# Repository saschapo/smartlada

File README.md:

# SmartLada — smart VAZ-2106 tail light

Firmware and custom hardware for a "smart" VAZ-2106 tail light: PWM dimming of the four
lamps (turn / brake / marker / reverse) with a local OLED menu, animation effects, and
**Zigbee control from a Yandex Station (Alice)**. Runs on a custom board that drops into
the light housing and is powered over **USB-C PD**.

Project page: **[smartlada.saschapo.me](https://smartlada.saschapo.me)** (source in [`site/`](site/)).

The current, primary firmware is **[`SmartLadaRevC/`](SmartLadaRevC/)** — it targets the
Rev C product board and is what the project ships. Everything else in the tree is either
the hardware design or earlier development stages (see [Lineage](#lineage)).

## Main firmware — SmartLadaRevC

ESP32-C6-WROOM-1 firmware for the Rev C board. Four PWM lamp channels (low-side MOSFET,
gamma + soft-start), an OLED menu with four buttons, pluggable effects, and a Zigbee end
device exposing five endpoints to Alice (four individual lamps + a "Fara" master/effects
device). Local control and Zigbee share one state (`config::s`, last-writer-wins).

Full details: **[`SmartLadaRevC/README.md`](SmartLadaRevC/README.md)**.

### Hardware (Rev C board)

<p align="center"><sub>Rev C, KiCad render. Top: ESP32-C6 module, buck, PD trigger, four lamp MOSFETs with
Faston outputs. Bottom: the silkscreen carries the VAZ-2106 tail-light exploded view from the parts
catalogue ("ФОНАРИ ЗАДНИЕ").</sub></p>

- **MCU:** ESP32-C6-WROOM-1-N16 (integrated on the board).
- **Power in:** USB-C PD, **12 V / 3 A trigger** (CH224K). 12 V feeds the lamps directly;
  a **TPS54202 buck** makes 3.3 V for the MCU/OLED. No 12 V → holds 5 V (logic alive, lamps dark).
  Recommended PSU: **COMMO Core** (a model with a 12 V/3 A PDO).
- **Lamp switches:** 4× AOD4184 N-MOSFET (low-side, gate active-high), outputs on **6.3 mm
  Faston tabs** with a common +12 V. Lamps: 12 V incandescent (e.g. 10+10+10+5 W).
- **UI:** SSD1315 OLED (I²C) + 4 buttons on connector J4, cabled out of the housing.
- **Diagnostics:** 6× red 0805 LEDs (4 channels + 12 V + 3.3 V); PG (power-good) → GPIO.

Board design (KiCad, BOM, fabrication): **[`custom_pcb/smartlada_revC/`](custom_pcb/smartlada_revC/)**.

### Build & flash

Zigbee end-device build, Serial over native USB:

```sh
FQBN="esp32:esp32:esp32c6:ZigbeeMode=ed,PartitionScheme=zigbee_8MB,CDCOnBoot=cdc,FlashSize=16M"
arduino-cli compile -b "$FQBN" SmartLadaRevC
arduino-cli upload  -b "$FQBN" -p /dev/cu.usbmodemXXXX SmartLadaRevC
```

Bench variant with the 2.4" TFT + encoder module in place of the OLED + keys: build flag
`UI_TFT`, see [`SmartLadaRevC/README.md`](SmartLadaRevC/README.md#bench-variant-24-tft--encoder-ui_tft).

Plan and resume notes: [`SmartLadaRevC/DEV_PLAN.md`](SmartLadaRevC/DEV_PLAN.md),
[`SmartLadaRevC/SESSION_HANDOFF.md`](SmartLadaRevC/SESSION_HANDOFF.md).

## Lineage

The firmware grew through several stages; the earlier ones are kept for reference:

- [`sketches/SmartLada/`](sketches/SmartLada/) — first bring-up bench on an **ESP8266**
  (calibration, OLED). Its `channels/` and `config/` layers seeded the ESP32 port.
- [`SmartLadaC6/`](SmartLadaC6/) — **ESP32-C6 on a MuseLab nanoESP32-C6** dev board:
  LEDC PWM, Wi-Fi AP + web UI, test modes. First C6 firmware.
- [`SmartLadaRevB/`](SmartLadaRevB/) — display-based firmware (OLED menu + effects) on the
  Rev B board; direct **predecessor to Rev C** (Rev C forks its `src/` layers).
- **[`SmartLadaRevC/`](SmartLadaRevC/)** — current product firmware (this board + Zigbee).

Hardware history lives under [`custom_pcb/`](custom_pcb/) (Rev A → Rev B → Rev C);
research and architecture notes under [`research/`](research/); experimental sketches
under [`sketches/`](sketches/).

## Project context (Russian)

Historical planning/context documents, kept in Russian on purpose:

- [`PROJECT_2106_SMART_LIGHT.md`](PROJECT_2106_SMART_LIGHT.md) — decisions, hardware, architecture, plan.
- [`VAZ2106_Smart_Lamp_Context.md`](VAZ2106_Smart_Lamp_Context.md) — earlier context document.
- [`TASK_smartlada_bench_esp8266.md`](TASK_smartlada_bench_esp8266.md) — ESP8266 bench spec (done).
- [`schematic_2106_ESP32.md`](schematic_2106_ESP32.md) — early wiring schematic.

> Chat and `.md` documentation are in Russian; firmware code, comments, and identifiers are in English.

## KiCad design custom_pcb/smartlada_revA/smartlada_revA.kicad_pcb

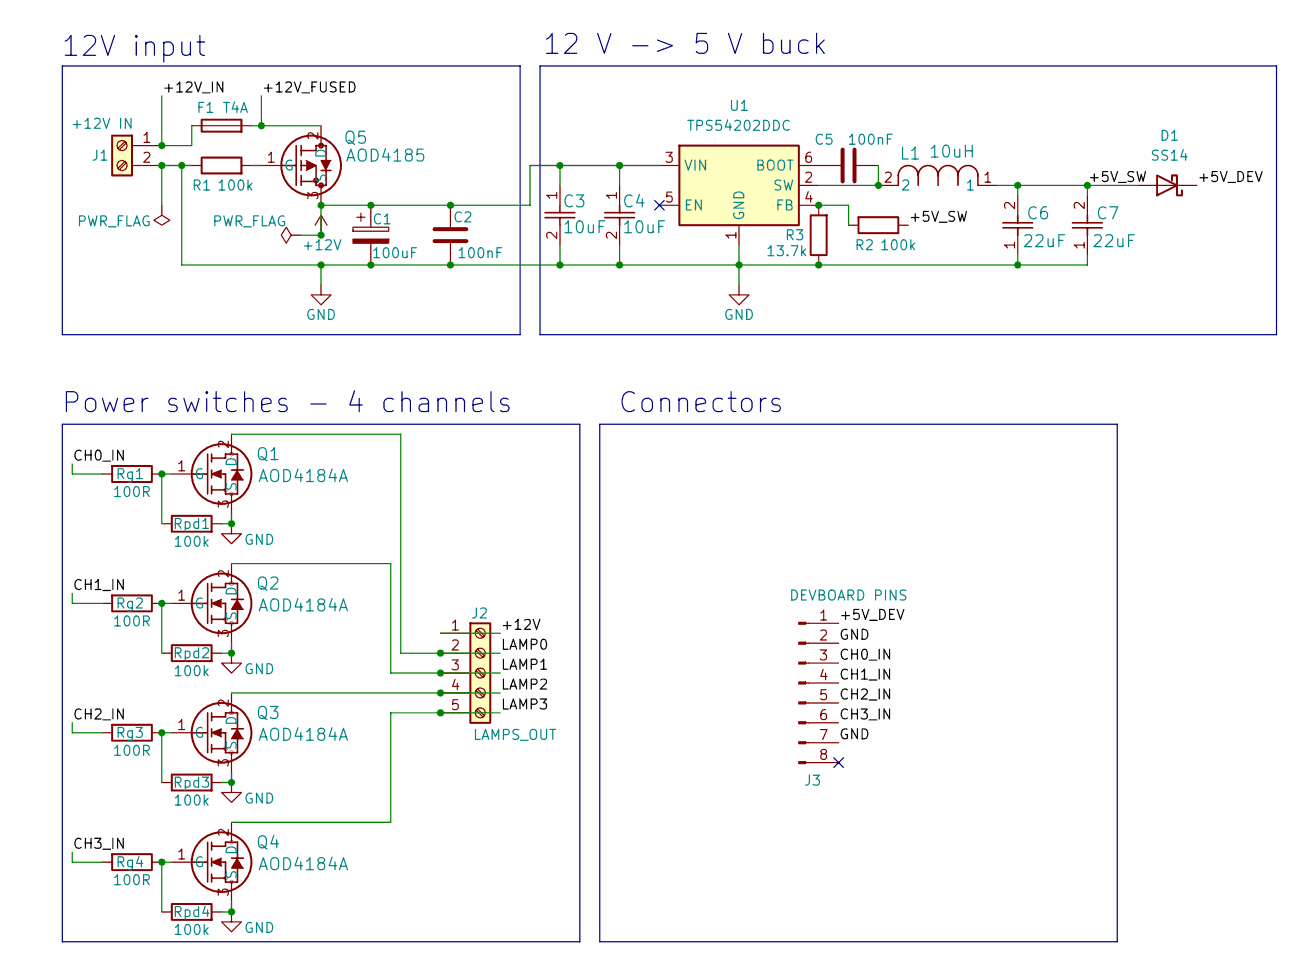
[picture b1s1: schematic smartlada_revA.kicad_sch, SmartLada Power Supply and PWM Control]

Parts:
C1: 100uF; CP_Radial_D6.3mm_P2.50mm; MPN EEUFR1E101
C2: 100nF; C_0805_2012Metric_Pad1.18x1.45mm_HandSolder; MPN GRM21BR71E104KA01L
C3, C4: 10uF; CAP_UMK325BJ106KM-P_TAY; MPN HLC1210X7R106K500N
C5: 100nF; C_0603_1608Metric_Pad1.08x0.95mm_HandSolder; MPN GRM188R72A104KA35D
C6, C7: 22uF; CAP_2012_TDK; MPN GRT21BR61E226ME13L
D1: SS14; D_SMA; MPN SS14-E3/61T
F1: T4A; Fuseholder_Cylinder-5x20mm_Schurter_0031_8201_Horizontal_Op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; MPN S1052-1
J1: +12V IN; TerminalBlock_MaiXu_MX126-5.0-02P_1x02_P5.00mm; MPN DG127-5.0-02P-14-00Z(H)
J2: LAMPS_OUT; TerminalBlock_Phoenix_MPT-0,5-5-2.54_1x05_P2.54mm_Horizontal; MPN DG308-2.54-05P-14-00ZH
J3: DEVBOARD PINS; PinHeader_1x08_P2.54mm_Vertical; MPN PLS-40 (alt L-KLS1-207-1-40-S)
L1: 10uH; IND_CDRH6D28NP-100NC_SUM; MPN CDRH6D28NP-100NC
Q1, Q2, Q3, Q4: AOD4184A; TO252_AOS; MPN AOD4184A
Q5: AOD4185; TO252_AOS; MPN AOD4185
R1, R2: 100k; R_0805_2012Metric_Pad1.20x1.40mm_HandSolder; MPN ERJP06F1003V
R3: 13.7k; R_0805_2012Metric_Pad1.20x1.40mm_HandSolder; MPN RC0805FR-0713K7L
Rg1, Rg2, Rg3, Rg4: 100R; R_0805_2012Metric_Pad1.20x1.40mm_HandSolder; MPN RT0805BRD07100RL
Rpd1, Rpd2, Rpd3, Rpd4: 100k; R_0805_2012Metric_Pad1.20x1.40mm_HandSolder; MPN ERJP06F1003V
U1: TPS54202DDC; SOT-23-6; MPN TPS54202DDCR

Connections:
+12V: C1.1, C2.1, C3.1, C4.1, J2.1, Q5.3 (S), U1.3 (VIN)
/+5V_DEV: D1.1 (K), J3.1
/+5V_SW: C6.2, C7.2, D1.2 (A), L1.1, R2.1
/+12V_FUSED: F1.2, Q5.2 (D)
/+12V_IN: F1.1, J1.1
/CH0_IN: J3.3, Rg1.2
/CH1_IN: J3.4, Rg2.2
/CH2_IN: J3.5, Rg3.2
/CH3_IN: J3.6, Rg4.2
/LAMP0: J2.2, Q1.2 (D)
/LAMP1: J2.3, Q2.2 (D)
/LAMP2: J2.4, Q3.2 (D)
/LAMP3: J2.5, Q4.2 (D)
GND: C1.2, C2.2, C3.2, C4.2, C6.1, C7.1, J1.2, J3.2, J3.7, Q1.3 (S), Q2.3 (S), Q3.3 (S), Q4.3 (S), R1.1, R3.1, Rpd1.2, Rpd2.2, Rpd3.2, Rpd4.2, U1.1 (GND)
unnamed: Q1.1 (G), Rg1.1, Rpd1.1
unnamed: Q2.1 (G), Rg2.1, Rpd2.1
unnamed: Q3.1 (G), Rg3.1, Rpd3.1
unnamed: Q4.1 (G), Rg4.1, Rpd4.1
unnamed: Q5.1 (G), R1.2
unnamed: C5.1, U1.6 (BOOT)
unnamed: R2.2, R3.2, U1.4 (FB)
unnamed: C5.2, L1.2, U1.2 (SW)

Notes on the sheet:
12V input
12 V -> 5 V buck
Connectors
Power switches - 4 channels

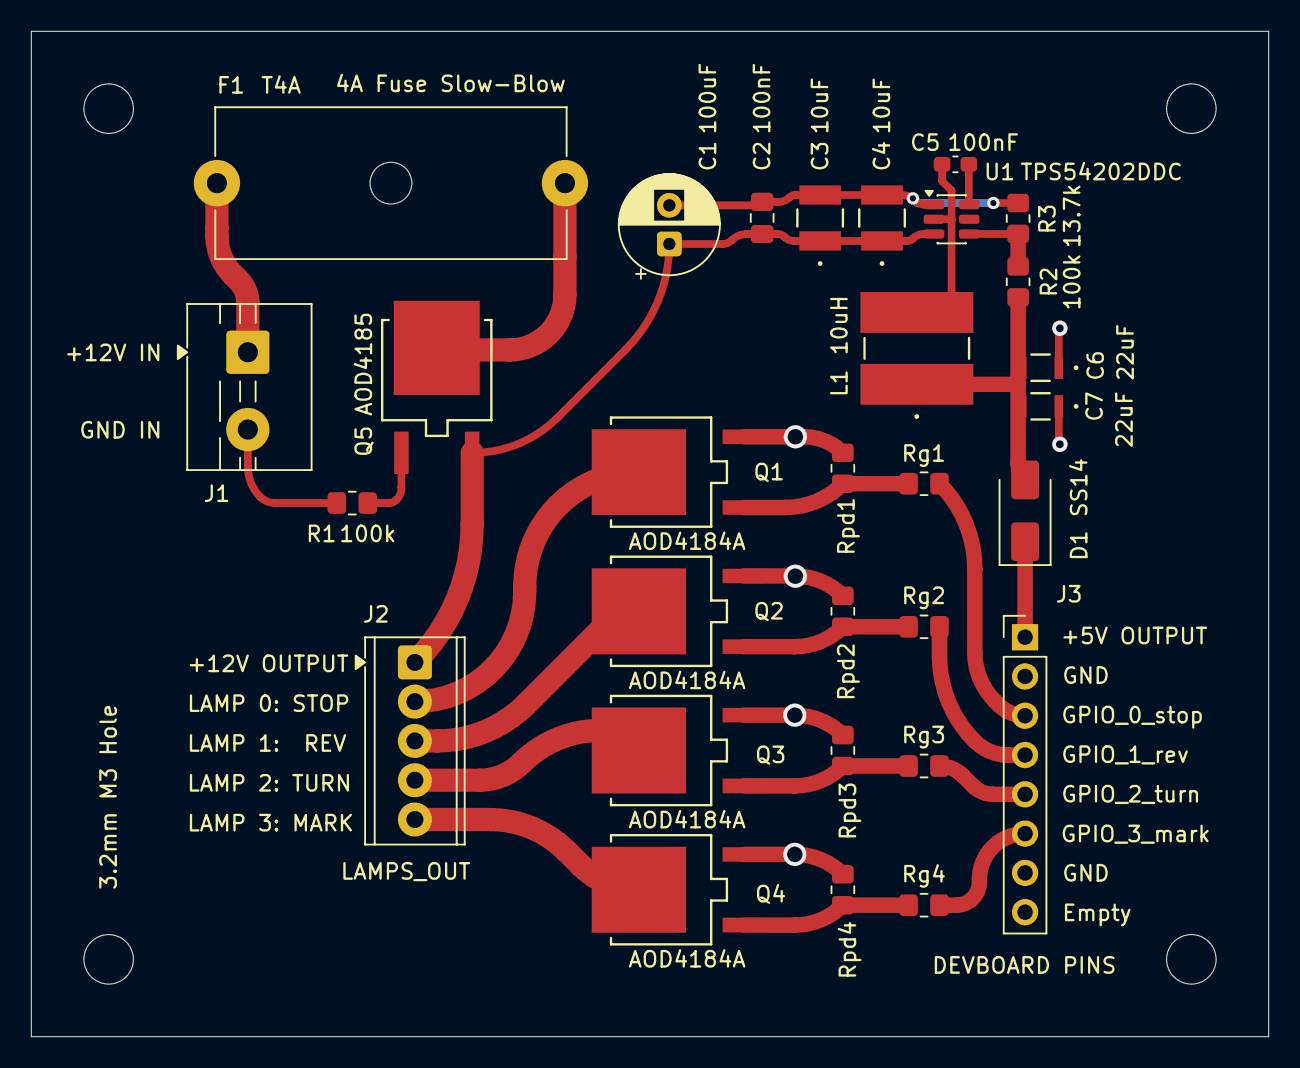
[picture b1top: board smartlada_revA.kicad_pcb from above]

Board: 2 copper layers, 80.0 x 65.0 mm, 34 parts (0 on the bottom side), 22 nets.

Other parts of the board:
H1, H2, H3: 3.2mm_M3; MountingHole_3.2mm_M3
H4: 3.2mm M3 Hole; MountingHole_3.2mm_M3

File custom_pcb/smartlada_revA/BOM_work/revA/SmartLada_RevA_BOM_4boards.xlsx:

SmartLada Rev A — комплектация на 4 платы
Источник: схема smartlada_revA (30 символов) x 4 платы. 'Нужно на 4' = формула 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
Ref | Описание / номинал | MPN | Производитель | Корпус | Кол-во/плата | Нужно на 4 | Заказать | Примечание
Q1-Q4 | MOSFET N-канал 40V (ключи ламп) | AOD4184A | Alpha & Omega | TO-252 | 4 | 16 | 20
Q5 | MOSFET P-канал (защита от переполюсовки) | AOD4185 | Alpha & Omega | TO-252 | 1 | 4 | 6 | докупить: в корзине 3
U1 | Buck 12->5V, 2A ADJ | TPS54202DDCR | Texas Instruments | SOT-23-6 | 1 | 4 | 6 | докупить: в корзине 3
L1 | Дроссель 10 uH экранир. | CDRH6D28NP-100NC | Sumida | 6x6 mm | 1 | 4 | 5 | докупить: в корзине 3
D1 | Диод Шоттки 1A 40V | SS14-E3/61T | Vishay | SMA | 1 | 4 | 8 | в корзине 20 — хватает
F1 (держатель) | Держатель предохр. 5x20 4A | S1052-1 | RUICHI | THT | 1 | 4 | 6 | OK: комплект (пластик. корпус + 2 контакта) = 1 держатель на плату
F1 (вставка) | Предохранитель T4A 5x20 медленный | FS-52GT-4.0/250 | GSL | 5x20 mm | 1 | 4 | 8 | расходник (сгорает на bring-up); докупить: в корзине 3
C1 | Электролит 100 uF 25V | EEUFR1E101 | Panasonic | D6.3 P2.5 | 1 | 4 | 6
C2 | Керам. 100 nF 25V | TCC0603X7R104K250CT | TCC | 0603 на 0805 | 1 | 4 | (в C5) | тот же TCC0603, что C5; 0603-корпус на площадке 0805 (осознанно); в общем заказе
C3,C4 | Керам. 10 uF 50V | HLC1210X7R106K500N | Walsin | 1210 | 2 | 8 | 12
C5 | Керам. 100 nF 25V (in-stock замена) | TCC0603X7R104K250CT | TCC | 0603 | 1 | 4 | 20 | C5+C2 = один TCC0603; заказ 20 на обе позиции; в наличии, от 1 шт
C6,C7 | Керам. 22 uF 25V | GRT21BR61E226ME13L | Murata | 0805 | 2 | 8 | 12
R1,R2,Rpd1-4 | Резистор 100k 1% | ERJP06F1003V | Panasonic | 0805 | 6 | 24 | 30 | докупить: в корзине 20 (нужно 24)
R3 | Резистор 13.7k 1% (делитель FB) | RC0805FR-0713K7L | Yageo | 0805 | 1 | 4 | 10
Rg1-4 | Резистор 100R (затвор) | RT0805BRD07100RL | Yageo | 0805 | 4 | 16 | 20
J1 | Клеммник 2 конт. 5.0 mm | DG127-5.0-02P-14-00Z(H) | Degson | THT | 1 | 4 | 6 | склад Platan 3 шт (нужно 4): взять 3 сейчас, +3 ДОЗАКАЗАТЬ позже
J2 | Клеммник 5 конт. 2.54 mm | DG308-2.54-05P-14-00ZH | Degson | THT | 1 | 4 | 6 | докупить: в корзине 3
J3 | Штырёк 1x40 2.54 mm (нужно 8 конт/плата) | PLS-40 (L-KLS1-207-1-40-S) | KLS | THT | 8 | 32 | 2 | единицы = контакты; заказать 2 линейки 1x40 (1 хватает на 32 конт)
Позиции AOD4184A (16), C6/C7 (8), Rg (16) в текущей корзине стоят ровно под нуж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
S1052-1: проверить, что 1 шт = комплект держателя (2 клипсы). Если продаётся по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
J3: PLS-40 считается линейками 1x40; на плату 8 контактов, на 4 платы = 32 из 4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
Заявка на изготовление плат — см. electroconnect_order_260721.md. Плат заказано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

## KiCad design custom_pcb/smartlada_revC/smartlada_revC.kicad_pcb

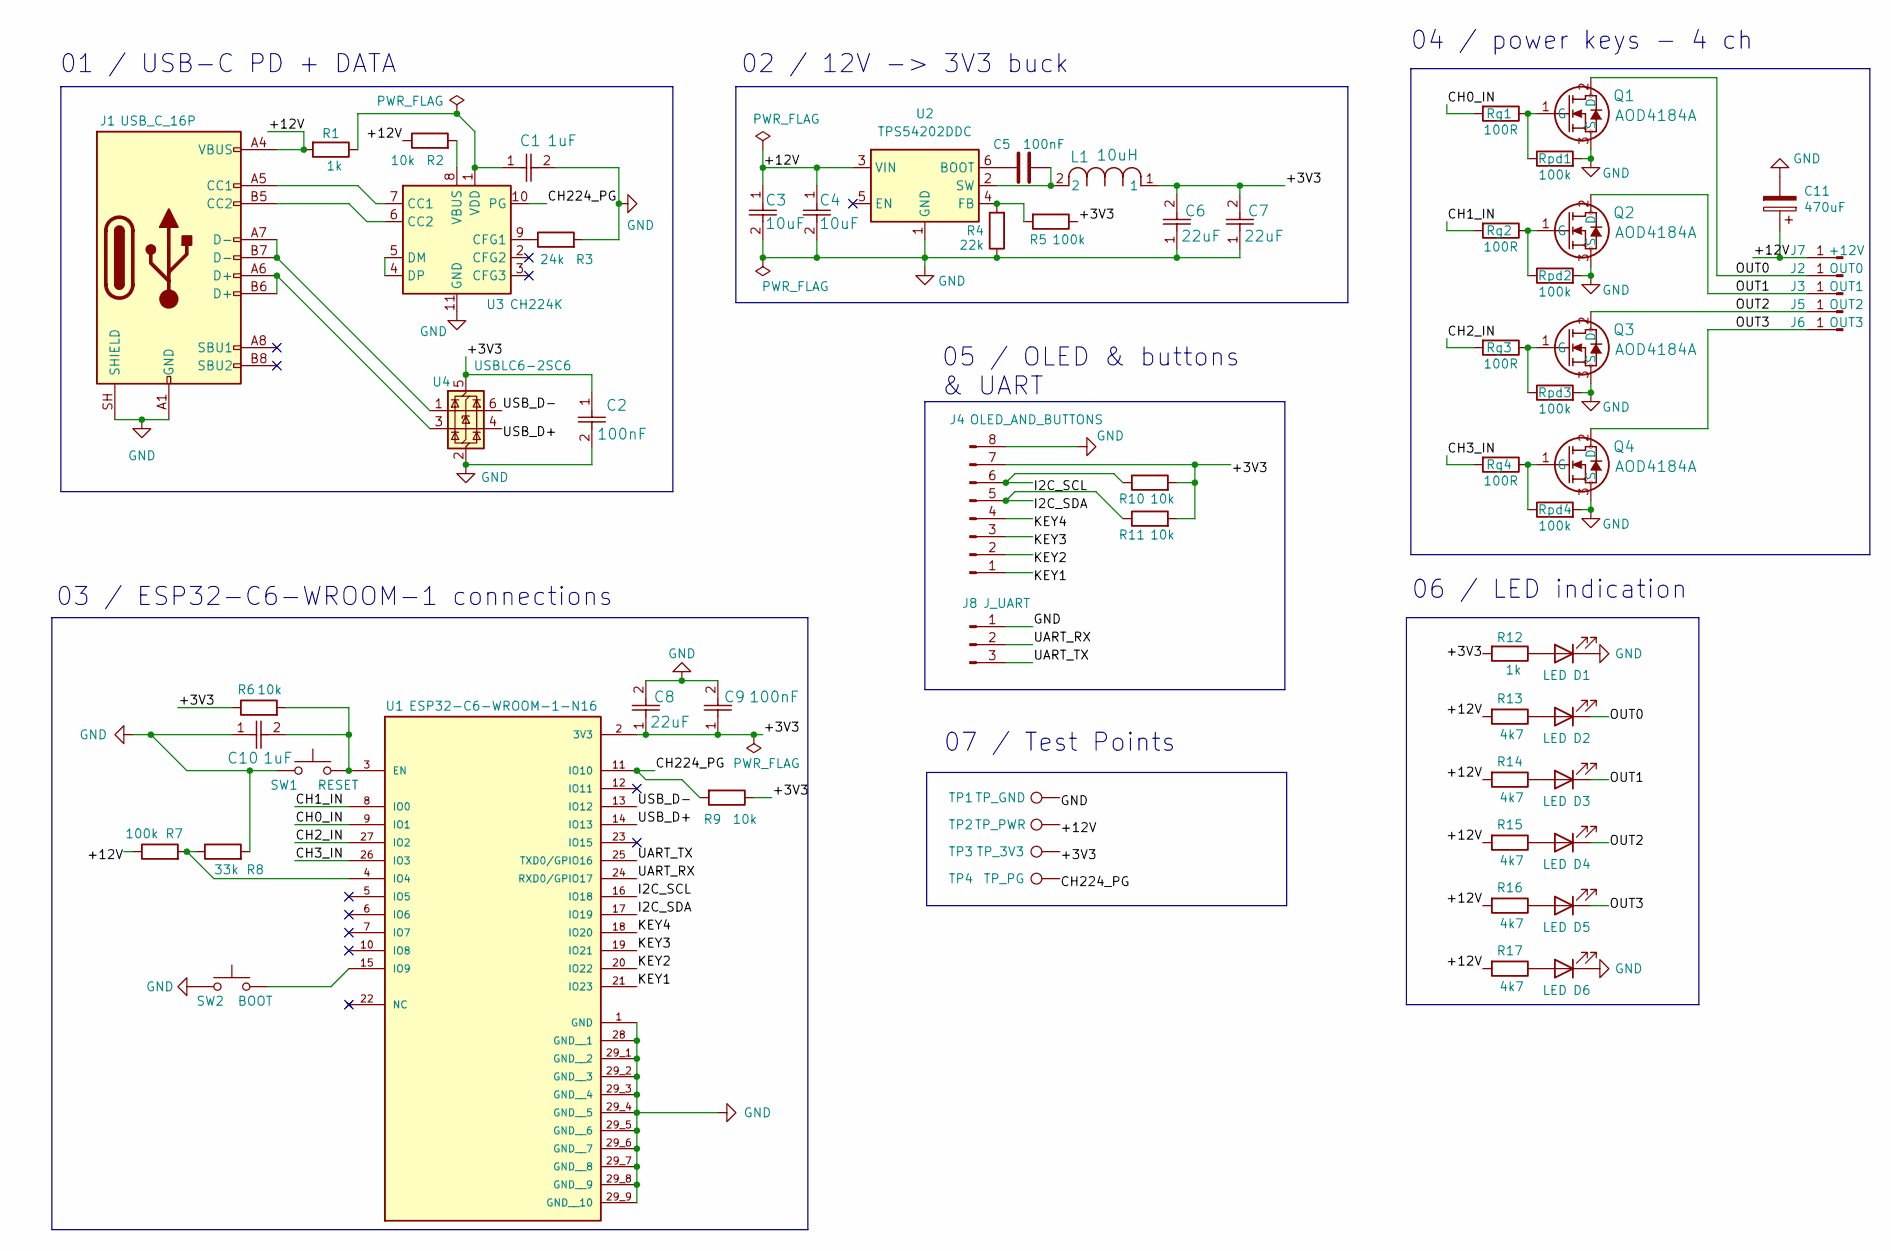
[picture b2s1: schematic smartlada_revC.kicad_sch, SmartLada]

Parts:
C1: 1uF; C_0805_2012Metric_Pad1.18x1.45mm_HandSolder; MPN GRM32ER71H106KA12L
C2: 100nF; C_0805_2012Metric_Pad1.18x1.45mm_HandSolder; MPN GRM32ER71H106KA12L
C3, C4: 10uF; C_1210_3225Metric_Pad1.33x2.70mm_HandSolder; MPN GRM32ER71H106KA12L
C5, C9: 100nF; C_0805_2012Metric_Pad1.18x1.45mm_HandSolder; MPN TCC0603X7R104K250CT
C6, C7, C8: 22uF; C_1210_3225Metric_Pad1.33x2.70mm_HandSolder; MPN GRT21BR61E226ME13L
C10: 1uF; C_0805_2012Metric_Pad1.18x1.45mm_HandSolder; MPN TCC0603X7R105K250CT
C11: 470uF; CP_Elec_10x10.5
D1, D2, D3, D4, D5, D6: LED; LED_0805_2012Metric_Pad1.15x1.40mm_HandSolder
J1: USB_C_16P; USB_C_Receptacle_HRO_TYPE-C-31-M-12
J2: OUT0; TE_1217754-1
J3: OUT1; TE_1217754-1
J4: OLED_AND_BUTTONS; PinHeader_1x08_P2.54mm_Horizontal; MPN PBS-40
J5: OUT2; TE_1217754-1
J6: OUT3; TE_1217754-1
J7: +12V; TE_1217754-1
J8: J_UART; PinHeader_1x03_P2.54mm_Horizontal
L1: 10uH; IND_CDRH6D28NP-100NC_SUM; MPN CDRH6D28NP-100NC
Q1, Q2, Q3, Q4: AOD4184A; TO252_AOS; MPN AOD4184A
R1, R12: 1k; R_0805_2012Metric_Pad1.20x1.40mm_HandSolder
R2, R9: 10k; R_0805_2012Metric_Pad1.20x1.40mm_HandSolder
R3: 24k; R_0805_2012Metric_Pad1.20x1.40mm_HandSolder
R4: 22k; R_0805_2012Metric_Pad1.20x1.40mm_HandSolder; MPN RC0805JR-0722KL
R5: 100k; R_0805_2012Metric_Pad1.20x1.40mm_HandSolder; MPN ERJP06F1003V
R6, R10, R11: 10k; R_0805_2012Metric_Pad1.20x1.40mm_HandSolder; MPN ERJ6ENF1002V
R7: 100k; R_0805_2012Metric_Pad1.20x1.40mm_HandSolder
R8: 33k; R_0805_2012Metric_Pad1.20x1.40mm_HandSolder
R13, R14, R15, R16, R17: 4k7; R_0805_2012Metric_Pad1.20x1.40mm_HandSolder
Rg1, Rg2, Rg3, Rg4: 100R; R_0805_2012Metric_Pad1.20x1.40mm_HandSolder; MPN RT0805BRD07100RL
Rpd1, Rpd2, Rpd3, Rpd4: 100k; R_0805_2012Metric_Pad1.20x1.40mm_HandSolder; MPN ERJP06F1003V
SW1: RESET; SW_SPST_Omron_B3FS-100xP; MPN 1-1825910-0
SW2: BOOT; SW_SPST_Omron_B3FS-100xP; MPN 1-1825910-0
TP1: TP_GND; TestPoint_THTPad_D2.0mm_Drill1.0mm
TP2: TP_PWR; TestPoint_THTPad_D2.0mm_Drill1.0mm
TP3: TP_3V3; TestPoint_THTPad_D2.0mm_Drill1.0mm
TP4: TP_PG; TestPoint_THTPad_D2.0mm_Drill1.0mm
U1: ESP32-C6-WROOM-1-N16; XCVR_ESP32-C6-WROOM-1-N16; MPN ESP32-C6-WROOM-1-N16
U2: TPS54202DDC; SOT-23-6_Handsoldering; MPN TPS54202DDCR
U3: CH224K; SSOP-10-1EP_3.9x4.9mm_P1mm_EP2.1x3.3mm_ThermalVias
U4: USBLC6-2SC6; SOT-23-6_Handsoldering

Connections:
/+3V3: C2.1, C6.2, C7.2, C8.1, C9.1, J4.7, L1.1, R5.1, R6.1, R9.1, R10.2, R11.2, R12.2, TP3.1 (1_1), U1.2 (3V3), U4.5 (VBUS)
/+12V: C3.1, C4.1, C11.1, J1.A4 (VBUS), J1.A9 (VBUS), J1.B4 (VBUS), J1.B9 (VBUS), J7.1 (Pin_1_1), R1.2, R2.1, R7.1, R13.2, R14.2, R15.2, R16.2, R17.2, TP2.1 (1_1), U2.3 (VIN)
/CH0_IN: Rg1.2, U1.9 (IO1)
/CH1_IN: Rg2.2, U1.8 (IO0)
/CH2_IN: Rg3.2, U1.27 (IO2)
/CH3_IN: Rg4.2, U1.26 (IO3)
/CH224_PG: R9.2, TP4.1 (1_1), U1.11 (IO10), U3.10 (PG)
/I2C_SCL: J4.6, R10.1, U1.16 (IO18)
/I2C_SDA: J4.5, R11.1, U1.17 (IO19)
/KEY1: J4.1, U1.21 (IO23)
/KEY2: J4.2, U1.20 (IO22)
/KEY3: J4.3, U1.19 (IO21)
/KEY4: J4.4, U1.18 (IO20)
/OUT0: D2.1 (K), J2.1 (Pin_1_1), Q1.2 (D)
/OUT1: D3.1 (K), J3.1 (Pin_1_1), Q2.2 (D)
/OUT2: D4.1 (K), J5.1 (Pin_1_1), Q3.2 (D)
/OUT3: D5.1 (K), J6.1 (Pin_1_1), Q4.2 (D)
/UART_RX: J8.2, U1.24 (RXD0/GPIO17)
/UART_TX: J8.3, U1.25 (TXD0/GPIO16)
/USB_D+: U1.14 (IO13), U4.4 (I/O2)
/USB_D-: U1.13 (IO12), U4.6 (I/O1)
GND: C1.2, C2.2, C3.2, C4.2, C6.1, C7.1, C8.2, C9.2, C10.1, C11.2, D1.1 (K), D6.1 (K), J1.A1 (GND), J1.A12 (GND), J1.B1 (GND), J1.B12 (GND), J1.SH (SHIELD), J4.8, J8.1, Q1.3 (S), Q2.3 (S), Q3.3 (S), Q4.3 (S), R3.2, R4.1, R8.2, Rpd1.2, Rpd2.2, Rpd3.2, Rpd4.2, SW1.1, SW2.1, TP1.1 (1_1), U1.1 (GND), U1.28 (GND__1), U1.29_1 (GND__2), U1.29_2 (GND__3), U1.29_3 (GND__4), U1.29_4 (GND__5), U1.29_5 (GND__6), U1.29_6 (GND__7), U1.29_7 (GND__8), U1.29_8 (GND__9), U1.29_9 (GND__10), U2.1 (GND), U3.11 (GND), U4.2 (GND)
unnamed: D1.2 (A), R12.1
unnamed: D2.2 (A), R13.1
unnamed: D3.2 (A), R14.1
unnamed: D4.2 (A), R15.1
unnamed: D5.2 (A), R16.1
unnamed: D6.2 (A), R17.1
unnamed: J1.A5 (CC1), U3.7 (CC1)
unnamed: J1.B5 (CC2), U3.6 (CC2)
unnamed: J1.A6 (D+), J1.B6 (D+), U4.3 (I/O2)
unnamed: J1.A7 (D-), J1.B7 (D-), U4.1 (I/O1)
unnamed: Q1.1 (G), Rg1.1, Rpd1.1
unnamed: Q2.1 (G), Rg2.1, Rpd2.1
unnamed: Q3.1 (G), Rg3.1, Rpd3.1
unnamed: Q4.1 (G), Rg4.1, Rpd4.1
unnamed: C10.2, R6.2, SW1.2, U1.3 (EN)
unnamed: R7.2, R8.1, U1.4 (IO4)
unnamed: SW2.2, U1.15 (IO9)
unnamed: C5.1, U2.6 (BOOT)
unnamed: R4.2, R5.2, U2.4 (FB)
unnamed: C5.2, L1.2, U2.2 (SW)
unnamed: R3.1, U3.9 (CFG1)
unnamed: U3.4 (DP), U3.5 (DM)
unnamed: R2.2, U3.8 (VBUS)
unnamed: C1.1, R1.1, U3.1 (VDD)

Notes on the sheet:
03 / ESP32-C6-WROOM-1 connections
05 / OLED & buttons & UART
04 / power keys - 4 ch
07 / Test Points
01 / USB-C PD + DATA
06 / LED indication
02 / 12V -> 3V3 buck

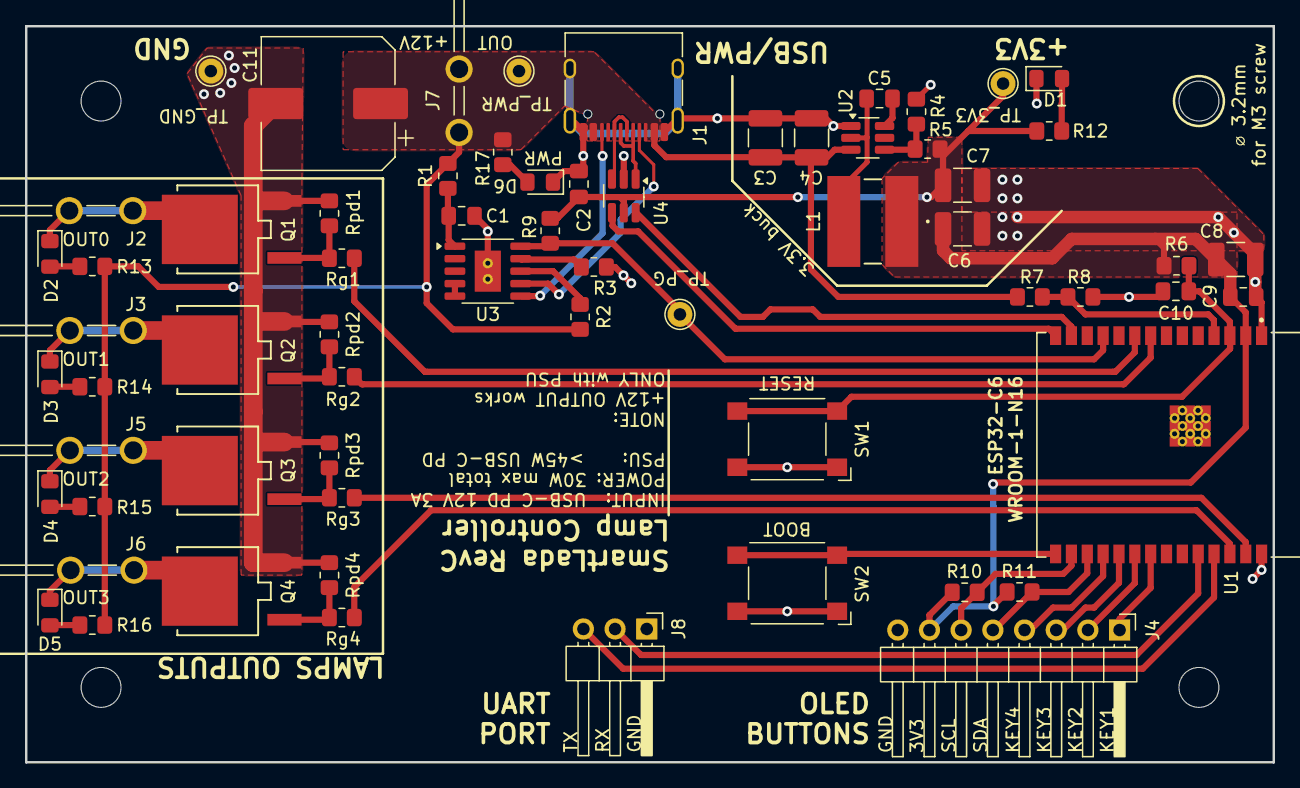
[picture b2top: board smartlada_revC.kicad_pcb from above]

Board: 2 copper layers, 100.0 x 59.0 mm, 69 parts (0 on the bottom side), 46 nets.

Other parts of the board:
HOLE1, HOLE1#2, HOLE1#3, HOLE1#4: MountingHole_3.2mm_M3

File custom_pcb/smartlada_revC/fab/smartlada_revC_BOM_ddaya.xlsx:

Name | Designator | Footprint | Supplier Part (LCSC)
1 µF 25V X7R 0805 | C1,C10 | C0805
100 nF 50V X7R 0805 | C2,C5,C9 | C0805
10 µF 25V X7R 1210 | C3,C4 | C1210
22 µF 16V X7R 1210 | C6,C7,C8 | C1210
470 µF 25V Alu SMD | C11 | Alu SMD 10x10.2
LED red 0805 | D1,D2,D3,D4,D5,D6 | LED0805
USB-C receptacle 16P (TYPE-C-31-M-12) THT | J1 | USB-C 16P
Faston 6.3 mm tab (63951-1) THT | J2,J3,J5,J6,J7 | Faston 6.3
Pin header 1x8 right-angle 2.54 mm THT | J4 | Header 1x8 RA
Pin header 1x3 right-angle 2.54 mm THT | J8 | Header 1x3 RA
CDRH6D28NP-100NC 10 µH | L1 | SMD 7x7mm
AOD4184A N-MOSFET 40V 50A | Q1,Q2,Q3,Q4 | TO-252 (DPAK)
1 kΩ ±5% 0805 | R1,R12 | R0805
10 kΩ ±1% 0805 | R2,R6,R9,R10,R11 | R0805
24 kΩ ±1% 0805 | R3 | R0805
22 kΩ ±1% 0805 | R4 | R0805
100 kΩ ±1% 0805 | R5,R7,Rpd1,Rpd2,Rpd3,Rpd4 | R0805
33 kΩ ±5% 0805 | R8 | R0805
4.7 kΩ ±1% 0805 | R13,R14,R15,R16,R17 | R0805
100 Ω ±5% 0805 | Rg1,Rg2,Rg3,Rg4 | R0805
Tactile switch 6x6 (B3FS1010P) SMD | SW1,SW2 | SW 6x6 SMD
ESP32-C6-WROOM-1-N16 module | U1 | WROOM module
TPS54202DDCR buck converter | U2 | SOT-23-6
CH224K USB-PD trigger | U3 | SSOP-10 (EP)
USBLC6-2SC6 USB ESD | U4 | SOT-23-6

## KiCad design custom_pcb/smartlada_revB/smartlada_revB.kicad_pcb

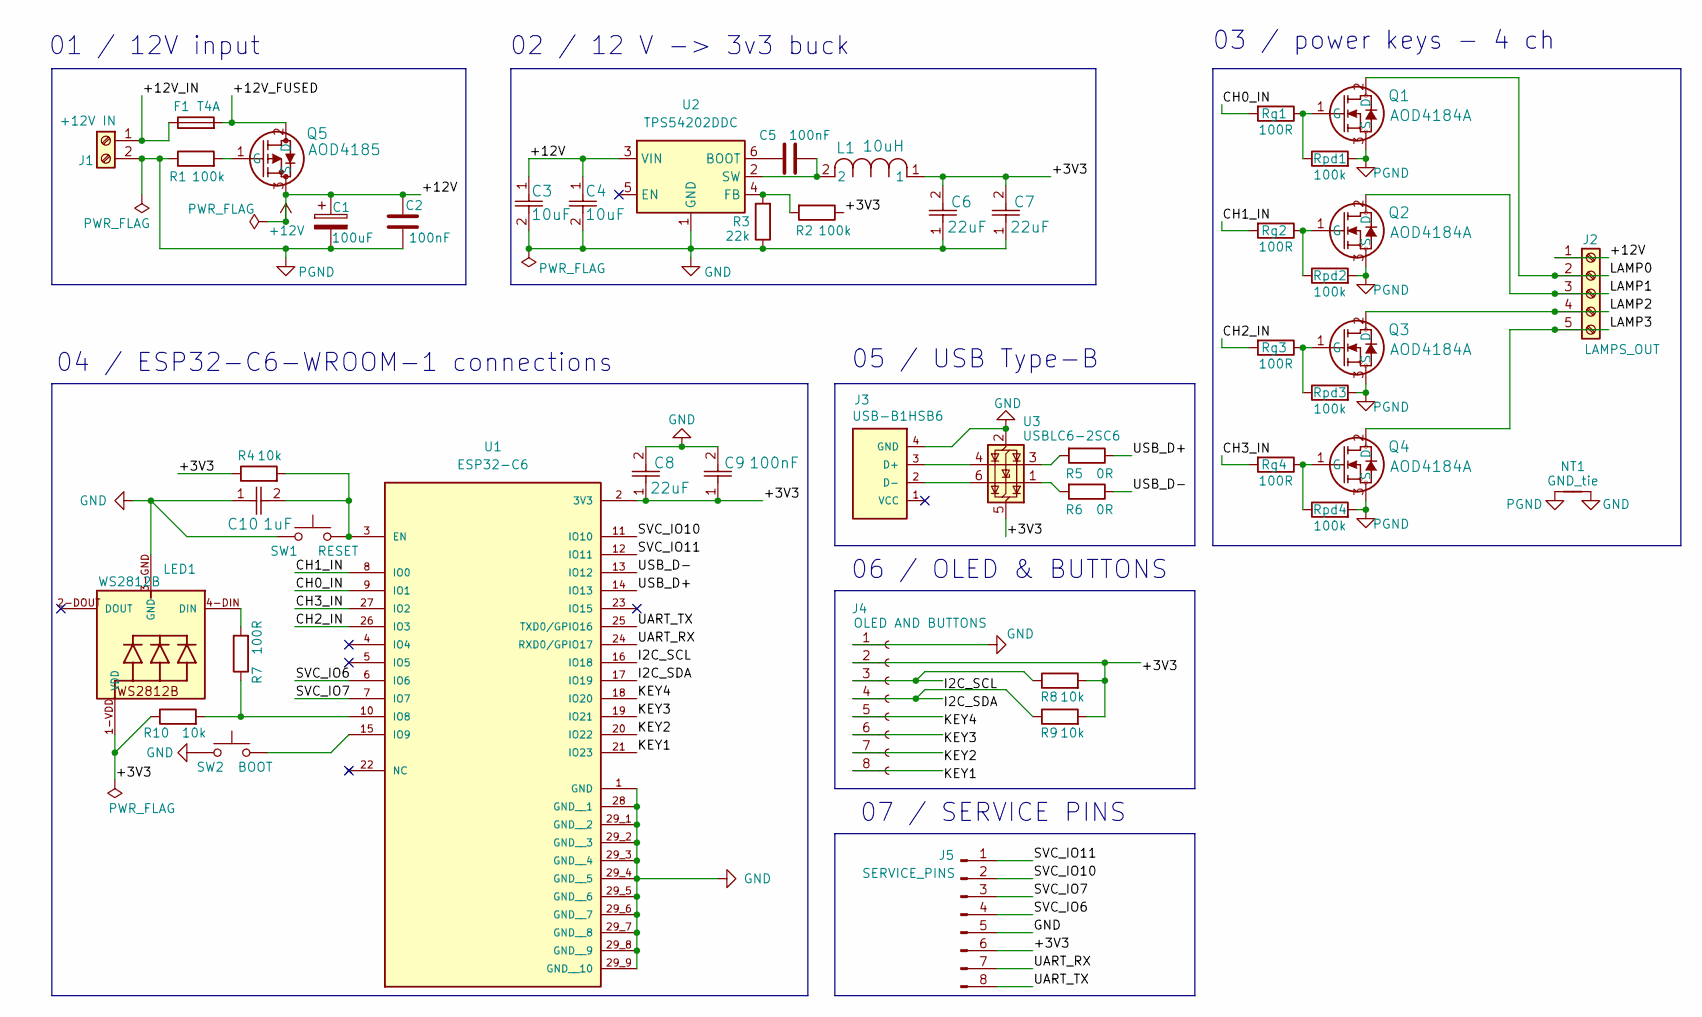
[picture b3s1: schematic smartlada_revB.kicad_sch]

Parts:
C1: 100uF; CP_Radial_D6.3mm_P2.50mm; MPN EEUFR1E101
C2: 100nF; C_0805_2012Metric_Pad1.18x1.45mm_HandSolder; MPN TCC0603X7R104K250CT
C3, C4: 10uF; C_1210_3225Metric_Pad1.33x2.70mm_HandSolder; MPN GRM32ER71H106KA12L
C5, C9: 100nF; C_0603_1608Metric_Pad1.08x0.95mm_HandSolder; MPN TCC0603X7R104K250CT
C6, C7, C8: 22uF; C_1210_3225Metric_Pad1.33x2.70mm_HandSolder; MPN GRT21BR61E226ME13L
C10: 1uF; C_0603_1608Metric_Pad1.08x0.95mm_HandSolder; MPN TCC0603X7R105K250CT
F1: T4A; Fuseholder_Cylinder-5x20mm_Schurter_0031_8201_Horizontal_Op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; MPN FS-52GT-4.0/250
J1: +12V IN; TerminalBlock_Phoenix_MKDS-1,5-2_1x02_P5.00mm_Horizontal; MPN DG127-5.0-02P-14-00Z(H)
J2: LAMPS_OUT; TerminalBlock_Phoenix_MPT-0,5-5-2.54_1x05_P2.54mm_Horizontal; MPN DG308-2.54-05P-14-00ZH
J3: USB-B1HSB6; OST_USB-B1HSB6; MPN USBB-1J-W
J4: OLED AND BUTTONS; PinSocket_1x08_P2.54mm_Vertical; MPN PBS-40
J5: SERVICE_PINS; PinHeader_1x08_P2.54mm_Vertical; MPN PLS-40
L1: 10uH; IND_CDRH6D28NP-100NC_SUM; MPN CDRH6D28NP-100NC
LED1: WS2812B; LED_WS2812B_PLCC4_5.0x5.0mm_P3.2mm; MPN WS2812B-V5
NT1: GND_tie; NetTie-2_THT_Pad0.3mm
Q1, Q2, Q3, Q4: AOD4184A; TO252_AOS; MPN AOD4184A
Q5: AOD4185; TO252_AOS; MPN AOD4185
R1, R2: 100k; R_0805_2012Metric_Pad1.20x1.40mm_HandSolder; MPN ERJP06F1003V
R3: 22k; R_0805_2012Metric_Pad1.20x1.40mm_HandSolder; MPN RC0805JR-0722KL
R4, R8, R9, R10: 10k; R_0805_2012Metric_Pad1.20x1.40mm_HandSolder; MPN ERJ6ENF1002V
R5, R6: 0R; R_0805_2012Metric_Pad1.20x1.40mm_HandSolder
R7: 100R; R_0805_2012Metric_Pad1.20x1.40mm_HandSolder; MPN RT0805BRD07100RL
Rg1, Rg2, Rg3, Rg4: 100R; R_0805_2012Metric_Pad1.20x1.40mm_HandSolder; MPN RT0805BRD07100RL
Rpd1, Rpd2, Rpd3, Rpd4: 100k; R_0805_2012Metric_Pad1.20x1.40mm_HandSolder; MPN ERJP06F1003V
SW1: RESET; SW4_1825910-F_TEC; MPN 1-1825910-0
SW2: BOOT; SW4_1825910-F_TEC; MPN 1-1825910-0
U1: ESP32-C6; XCVR_ESP32-C6-WROOM-1-N8; MPN ESP32-C6-WROOM-1-N16
U2: TPS54202DDC; SOT-23-6; MPN TPS54202DDCR
U3: USBLC6-2SC6; SOT-23-6_Handsoldering; MPN USBLC6-2SC6

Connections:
+12V: C1.1, C2.1, C3.1, C4.1, J2.1, Q5.3 (S), U2.3 (VIN)
/+3V3: C6.2, C7.2, C8.1, C9.1, J4.2, J5.6, L1.1, LED1.1-VDD (VDD), R2.1, R4.1, R8.2, R9.2, R10.1, U1.2 (3V3), U3.5 (VBUS)
/+12V_FUSED: F1.2, Q5.2 (D)
/+12V_IN: F1.1, J1.1
/CH0_IN: Rg1.2, U1.9 (IO1)
/CH1_IN: Rg2.2, U1.8 (IO0)
/CH2_IN: Rg3.2, U1.26 (IO3)
/CH3_IN: Rg4.2, U1.27 (IO2)
/I2C_SCL: J4.3, R8.1, U1.16 (IO18)
/I2C_SDA: J4.4, R9.1, U1.17 (IO19)
/KEY1: J4.8, U1.21 (IO23)
/KEY2: J4.7, U1.20 (IO22)
/KEY3: J4.6, U1.19 (IO21)
/KEY4: J4.5, U1.18 (IO20)
/LAMP0: J2.2, Q1.2 (D)
/LAMP1: J2.3, Q2.2 (D)
/LAMP2: J2.4, Q3.2 (D)
/LAMP3: J2.5, Q4.2 (D)
/SVC_IO6: J5.4, U1.6 (IO6)
/SVC_IO7: J5.3, U1.7 (IO7)
/SVC_IO10: J5.2, U1.11 (IO10)
/SVC_IO11: J5.1, U1.12 (IO11)
/UART_RX: J5.7, U1.24 (RXD0/GPIO17)
/UART_TX: J5.8, U1.25 (TXD0/GPIO16)
/USB_D+: R5.1, U1.14 (IO13)
/USB_D-: R6.1, U1.13 (IO12)
GND: C3.2, C4.2, C6.1, C7.1, C8.2, C9.2, C10.1, J3.4 (GND), J4.1, J5.5, LED1.3-GND (GND), NT1.2, R3.1, SW1.1, SW2.1, U1.1 (GND), U1.28 (GND__1), U1.29_1 (GND__2), U1.29_2 (GND__3), U1.29_3 (GND__4), U1.29_4 (GND__5), U1.29_5 (GND__6), U1.29_6 (GND__7), U1.29_7 (GND__8), U1.29_8 (GND__9), U1.29_9 (GND__10), U2.1 (GND), U3.2 (GND)
unnamed: J3.3 (D+), U3.4 (I/O2)
unnamed: J3.2 (D-), U3.6 (I/O1)
unnamed: LED1.4-DIN (DIN), R7.2
unnamed: Q1.1 (G), Rg1.1, Rpd1.1
unnamed: Q2.1 (G), Rg2.1, Rpd2.1
unnamed: Q3.1 (G), Rg3.1, Rpd3.1
unnamed: Q4.1 (G), Rg4.1, Rpd4.1
unnamed: Q5.1 (G), R1.2
unnamed: R5.2, U3.3 (I/O2)
unnamed: R6.2, U3.1 (I/O1)
unnamed: C10.2, R4.2, SW1.2, U1.3 (EN)
unnamed: R7.1, R10.2, U1.10 (IO8)
unnamed: SW2.2, U1.15 (IO9)
unnamed: C5.1, U2.6 (BOOT)
unnamed: R2.2, R3.2, U2.4 (FB)
unnamed: C5.2, L1.2, U2.2 (SW)
PGND: C1.2, C2.2, J1.2, NT1.1, Q1.3 (S), Q2.3 (S), Q3.3 (S), Q4.3 (S), R1.1, Rpd1.2, Rpd2.2, Rpd3.2, Rpd4.2

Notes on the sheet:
04 / ESP32-C6-WROOM-1 connections
06 / OLED & BUTTONS
03 / power keys - 4 ch
01 / 12V input
05 / USB Type-B
07 / SERVICE PINS
02 / 12 V -> 3v3 buck
